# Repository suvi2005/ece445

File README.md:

# ece445

digit: will hold anything related to the project: pcb, code, designs etc.
lab-notebook: (self-explanatory)

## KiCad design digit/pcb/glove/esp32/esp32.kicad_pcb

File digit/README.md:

DIGIT: Digital Interactive Gesture Interface for Teleoperation

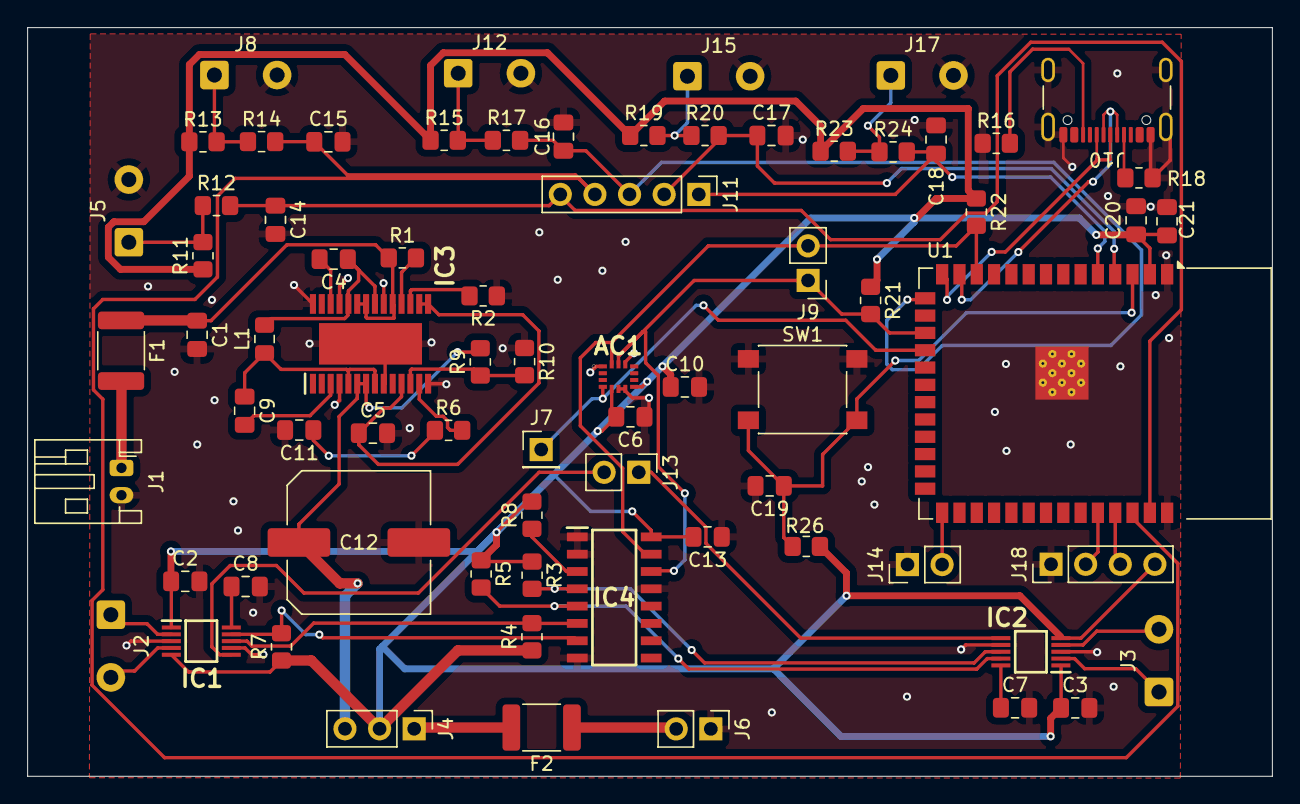
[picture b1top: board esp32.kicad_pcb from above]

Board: 2 copper layers, 91.3 x 54.9 mm, 73 parts (0 on the bottom side), 51 nets.

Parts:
AC1: LSM6DSOXTR; LGA-14_1
C1: 10µF; C_0805_2012Metric_Pad1.18x1.45mm_HandSolder
C2, C3, C7, C8: 1µF; C_0805_2012Metric_Pad1.18x1.45mm_HandSolder
C4, C9, C13: 0.1µF; C_0805_2012Metric_Pad1.18x1.45mm_HandSolder
C5: 4.7µF; C_0805_2012Metric_Pad1.18x1.45mm_HandSolder
C6, C10, C14, C15, C16, C17, C18: 100nF; C_0805_2012Metric_Pad1.18x1.45mm_HandSolder
C11: 470pF; C_0805_2012Metric_Pad1.18x1.45mm_HandSolder
C12: 150µF; C_Elec_10x10.2
C19, C20: 0.1uF; C_0805_2012Metric_Pad1.18x1.45mm_HandSolder
C21: 22uF; C_0805_2012Metric_Pad1.18x1.45mm_HandSolder
F1, F2: MF-MSMF075-2; Fuse_1812_4532Metric_Pad1.30x3.40mm_HandSolder
IC1, IC2: DRV2605LDGSR; SOP50P490X110-10N
IC3: LTC3119EFE#PBF; SOP65P640X120-29N
IC4: TCA9546ADR; SOIC127P600X175-16N
J1: Conn_01x02_Pin; JST_PH_S2B-PH-K_1x02_P2.00mm_Horizontal
J2, J3, J5, J8, J12, J15, J17: Conn_01x02_Pin; SolderWire-0.5sqmm_1x02_P4.6mm_D0.9mm_OD2.1mm
J4: Conn_01x03_Pin; PinHeader_1x03_P2.54mm_Vertical
J6, J9, J13, J14: Conn_01x02_Pin; PinHeader_1x02_P2.54mm_Vertical
J7: Conn_01x01_Pin; PinHeader_1x01_P2.54mm_Vertical
J10: USB_C_Receptacle_USB2.0_16P; USB_C_Receptacle_GCT_USB4105-xx-A_16P_TopMnt_Horizontal
J11: Conn_01x05_Pin; PinHeader_1x05_P2.54mm_Vertical
J18: Conn_01x04_Pin; PinHeader_1x04_P2.54mm_Vertical
L1: 2.2µH; L_0805_2012Metric_Pad1.15x1.40mm_HandSolder
R1, R10: 100k; R_0805_2012Metric_Pad1.20x1.40mm_HandSolder
R2: 48.7k; R_0805_2012Metric_Pad1.20x1.40mm_HandSolder
R3, R4, R5, R7, R8, R21, R22, R26: 10k; R_0805_2012Metric_Pad1.20x1.40mm_HandSolder
R6: 52.3k; R_0805_2012Metric_Pad1.20x1.40mm_HandSolder
R9: 316k; R_0805_2012Metric_Pad1.20x1.40mm_HandSolder
R11, R13, R15, R19, R23: 22k; R_0805_2012Metric_Pad1.20x1.40mm_HandSolder
R12, R14, R17, R20, R24: 1k; R_0805_2012Metric_Pad1.20x1.40mm_HandSolder
R16, R18: 5.1k; R_0805_2012Metric_Pad1.20x1.40mm_HandSolder
SW1: SW_Push; SW_SPST_PTS645
U1: ESP32-S3-WROOM-1

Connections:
+3.7V: F1.2, J1.1
/BB_3V3: C12.1, IC3.6 (PVOUT_1), IC3.7 (PVOUT_2), J4.3, R9.2
/BOOT: J14.2, U1.27 (IO0)
/Dn: J10.A7 (D-), J10.B7 (D-), U1.13 (USB_D-)
/Dp: J10.A6 (D+), J10.B6 (D+), U1.14 (USB_D+)
/EN: C19.1, R26.1, SW1.2, U1.3 (EN)
/EXT_3V3: F2.1, J6.2
/FLEX1_ADC: C14.1, J11.5, R12.2, U1.39 (IO1)
/FLEX2_ADC: C15.1, J11.4, R14.2, U1.38 (IO2)
/FLEX3_ADC: C16.1, J11.3, R17.2, U1.15 (IO3)
/FLEX4_ADC: C17.1, J11.2, R20.2, U1.4 (IO4)
/FLEX5_ADC: C18.1, J11.1, R24.2, U1.5 (IO5)
/HAPTIC_DRIVER1_EN: IC1.6 (VDD/NC), J13.2
/HAPTIC_DRIVER2_EN: IC2.6 (VDD/NC), J13.1
/I2C_SCL: AC1.13 (SCL), IC4.14 (SCL), J9.1, R21.2, U1.17 (IO9)
/I2C_SDA: AC1.14 (SDA), IC4.15 (SDA), J9.2, R22.2, U1.12 (IO8)
/IMU_INT1: AC1.4 (INT1), J7.1, U1.18 (IO10)
/UART_RX: J18.2, U1.36 (RXD0)
/UART_TX: J18.3, U1.37 (TXD0)
GND: AC1.1 (SDO/SA0), AC1.6 (GND_1), AC1.7 (GND_2), AC1.12 (CS), C1.2, C2.2, C3.2, C5.2, C6.1, C7.2, C8.2, C10.2, C11.2, C12.2, C13.1, C14.2, C15.2, C16.2, C17.2, C18.2, C19.2, C20.2, C21.2, IC1.3 (SDA), IC1.7 (OUT+), IC2.3 (SDA), IC2.7 (OUT+), IC3.4 (PGND_1), IC3.9 (PGND_2), IC3.14 (SGND), IC3.20 (PGND_3), IC3.25 (PGND_4), IC3.28 (PWM/SYNC), IC3.29 (PGND_5), IC4.1 (A0), IC4.2 (A1), IC4.8 (GND), IC4.13 (A2), J1.2, J5.2, J6.1, J8.2, J10.A1 (GND), J10.A12 (GND), J10.B1 (GND), J10.B12 (GND), J10.S1 (SHIELD), J12.2, J14.1, J15.2, J17.2, J18.1, R2.1, R10.1, R16.1, R18.1, SW1.1, U1.1 (GND), U1.40 (GND), U1.41 (GND)
unnamed: C11.1, R6.1
unnamed: IC1.8 (GND), IC4.6 (SD1), R4.2
unnamed: IC1.4 (IN/TRIG), J2.2
unnamed: IC1.9 (OUT-), IC4.7 (SC1), R7.2
unnamed: IC1.2 (SCL), J2.1
unnamed: C8.1, IC1.10 (VDD)
unnamed: IC2.8 (GND), IC4.4 (SD0), R3.2
unnamed: IC2.4 (IN/TRIG), J3.2
unnamed: IC2.9 (OUT-), IC4.5 (SC0), R5.2
unnamed: IC2.2 (SCL), J3.1
unnamed: C7.1, IC2.10 (VDD)
unnamed: C4.2, IC3.26 (BST1)
unnamed: C9.2, IC3.3 (BST2)
unnamed: IC3.12 (FB), R9.1, R10.2
unnamed: C5.1, IC3.11 (SVCC), IC3.15 (MPPC), IC3.16 (VCC)
unnamed: C1.1, F1.1, IC3.19 (VIN), IC3.22 (PVIN_1), IC3.23 (PVIN_2), R1.1
unnamed: IC3.17 (RT), R2.2
unnamed: IC3.18 (RUN), R1.2
unnamed: C4.1, IC3.21 (SW1_1), IC3.24 (SW1_2), L1.2
unnamed: C9.1, IC3.5 (SW2_1), IC3.8 (SW2_2), L1.1
unnamed: IC3.13 (VC), R6.2
unnamed: IC4.3 (~RESET), R8.1
unnamed: F2.2, J4.1
unnamed: J5.1, R11.2, R12.1
unnamed: J8.1, R13.2, R14.1
unnamed: J10.A5 (CC1), R18.2
unnamed: J10.B5 (CC2), R16.2
unnamed: J12.1, R15.2, R17.1
unnamed: J15.1, R19.2, R20.1
unnamed: J17.1, R23.2, R24.1
SYS_3V3: AC1.5 (VDDIO), AC1.8 (VDD), C2.1, C3.1, C6.2, C10.1, C13.2, C20.1, C21.1, IC1.1 (REG), IC1.5 (EN), IC2.1 (REG), IC2.5 (EN), IC4.16 (VCC), J4.2, J18.4, R3.1, R4.1, R5.1, R7.1, R8.2, R11.1, R13.1, R15.1, R19.1, R21.1, R22.1, R23.1, R26.2, U1.2 (3V3)

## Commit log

2026-02-04 Intial folder structure nothing too deep
2026-02-24 Update project name to 'Digital Interactive Gesture Interface'
2026-03-10 Added test code for ESP32 BLE
2026-03-10 Added a note to the test README
2026-03-11 Basic BLE from esp32 to nrf. Lidar data is sent over successfully
2026-03-11 For the BLE transfer test reduced the traffic to make the LED more responsive
2026-04-05 added the code for camera, ToF, and motor driver
2026-04-05 added bluetooth code
2026-04-19 updated the robot code to connect the esp32 pcb
2026-04-20 Basic TOF discovery on the robot and ble comm between robot and glove seems to be working
2026-04-20 Added the PCB designs
2026-04-20 uploading code for glove
2026-04-20 Ported the Arduino code over to ESP-IDF for the glove firmware
2026-04-20 Changed the robot code to be able to ignore invalid sensor value
2026-04-20 changed web server code to have compatibility with esp idf and added left and right stopping with turning
2026-04-23 Changed directory names to be proper
2026-04-25 added flick with LED + RECORD and speed with movement
2026-04-26 Added final firmware for robot and glove. Robot and glove can now interface with multiple gestures
2026-04-26 fixed some build folder problem
2026-04-26 Changed the PWM for the motor
2026-04-27 Changed PWM, haptic motors, and flex sensor threshold. (GOLD VERSION)
2026-05-04 submitting my lab notebook
2026-05-05 removed duplicate video and added all relevant photos
2026-05-06 Test
2026-05-06 testing
2026-05-07 Notebook completed
2026-05-08 Lab notebook uploaded
